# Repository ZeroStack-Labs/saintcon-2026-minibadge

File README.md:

<h1><span style="color:#A3FF12">ZeroStack Labs SAINTCON 2026 MiniBadge</span></h1>

A custom SAINTCON-compatible MiniBadge designed as a ZeroStack Labs hardware/firmware learning project.

This project combines PCB design, embedded firmware, 3D printing, mechanical design, and custom fabrication into a small badge intended for use with the SAINTCON MiniBadge ecosystem.

The finished design features an ATtiny402 microcontroller, two green LEDs, a custom two-color 3D-printed topper, and a dedicated UPDI programming/test jig.

> **Project status:** Prototype / active development  
> The PCB has been ordered and the 3D-printed topper design has reached a successful production prototype.

---

## Features

- SAINTCON MiniBadge-compatible footprint and pinout
- Custom 25.4 mm × 25.4 mm PCB
- ATtiny402 microcontroller
- Two individually controlled green LEDs
- UPDI programming test point
- Custom ZeroStack Labs silkscreen artwork
- Two-color 3D-printed topper
- Acid-green translucent logo/inlay
- Black structural backing layer
- M2 self-tapping mounting screws
- Custom 3D-printed programming jig
- Planned LED breathing / animation firmware

---

## Project Goals

This project started as a way to learn more about:

- KiCad PCB design
- Embedded microcontrollers
- UPDI programming
- Surface-mount soldering
- PCB fabrication
- Multi-color 3D printing
- Mechanical integration between a PCB and printed topper
- Firmware development for small embedded devices

The design files are being published so others can study the project, modify it, and create their own MiniBadge variations.

---

## Hardware

### Microcontroller

The badge uses a **Microchip ATtiny402-SSN** in an SOIC-8 package.

| ATtiny402 Pin | Function               |
| ------------- | ---------------------- |
| VCC           | +3.3 V                 |
| GND           | Ground                 |
| PA1           | LED 1                  |
| PA2           | LED 2                  |
| PA0 / UPDI    | Programming test point |

Unused pins are intentionally left unconnected.

### LEDs

Two green 1206 LEDs are driven through 220 ohm current-limiting resistors.

Approximate LED current:

```text
(3.3 V - 2.1 V) / 220 ohm ≈ 5.5 mA
```

### Decoupling

A 0.1 uF ceramic capacitor is placed close to the ATtiny402 VCC and GND pins.

---

## MiniBadge Interface

The PCB follows the open MiniBadge pinout and interface convention.

Relevant pins used by this design include:

| Pin | Function |
| --- | -------- |
| 1   | VBATT    |
| 2   | GND      |
| 7   | +3V3     |
| 8   | GND      |
| 9   | CLK      |
| 10  | NC       |
| 15  | +3V3     |
| 16  | GND      |

Only the required header positions are intended to be populated, while the PCB retains the complete 16-hole MiniBadge footprint.

> **Important:** VBATT and +3V3 are not connected together.

---

## PCB

The PCB was designed in **KiCad 10**.

### Board dimensions

- 25.4 mm × 25.4 mm
- Rounded square outline
- 2 mm corner radius
- Three 2.2 mm mounting holes

### Fabrication

The first production run was ordered through **OSH Park** using the **After Dark** process.

Fabrication outputs include:

- Front copper
- Back copper
- Front solder mask
- Back solder mask
- Front silkscreen
- Back silkscreen
- Edge cuts
- Plated through-hole drill file
- Non-plated through-hole drill file

---

## 3D-Printed Topper

The topper is designed as a two-color print consisting of:

1. A black structural body
2. A translucent green ZeroStack Labs artwork/inlay

The successful production prototype is:

**V10.1**

### Production files

```text
ZeroStack_Topper_FINAL_v10_1_BLACK_BODY.stl
ZeroStack_Topper_FINAL_v10_1_GREEN_INLAY.stl
```

### Printing workflow

The two STL files are imported into **Flash Studio**, assembled as separate objects, and assigned different filaments.

Recommended orientation:

- **Face down**
- **Mounting posts up**

Printing face-down allows the visible surface to inherit the PEI build plate texture while keeping layer lines on the hidden rear surface.

### Topper construction

- Total top plate thickness: 2.0 mm
- Solid black backing: 0.5 mm
- Green inlay depth: 1.5 mm
- Mounting post diameter: approximately 4.5 mm
- M2 self-tapping pilot hole: approximately 1.7 mm

The mounting posts use a reinforced/tapered base to improve print reliability.

---

## Programming Jig

A custom 3D-printed jig was created to simplify programming and testing.

The jig uses the MiniBadge header locations to position the PCB and provides access to the ATtiny402 UPDI test point.

The intended programming setup uses:

- MiniBadge +3V3
- MiniBadge GND
- One pogo pin contacting the UPDI test pad

An Arduino Uno R3 may be used as a UPDI programmer with suitable firmware/software.

Programming documentation will be added as the firmware workflow is finalized.

---

## Firmware

Firmware is planned for the ATtiny402 to control both LEDs.

Initial goals include:

- Smooth breathing animation
- Adjustable brightness
- Adjustable breathing speed
- Optional alternating LED phase
- Simple constants for easy customization

---

## Repository Structure

```text
saintcon-2026-minibadge/
├── README.md
├── LICENSE
├── hardware/
│   ├── pcb/
│   ├── gerbers/
│   └── bom/
├── mechanical/
│   ├── topper/
│   └── programming-jig/
├── firmware/
├── docs/
└── assets/
```

---

## Bill of Materials

| Qty / Badge        | Component           | Part                    |
| ------------------ | ------------------- | ----------------------- |
| 1                  | Microcontroller     | Microchip ATtiny402-SSN |
| 1                  | 0.1 uF capacitor    | KEMET C0805C104K8RACTU  |
| 2                  | 220 ohm resistor    | Yageo RC1206FR-07220RL  |
| 2                  | Green LED           | Kingbright APTL3216CGCK |
| 4 × 2-pin sections | 2.54 mm male header | Sullins PREC040SAAN-RC  |

Additional parts include mounting screws and the printed topper.

---

## Assembly Notes

Recommended assembly order:

1. Inspect the bare PCB.
2. Solder the ATtiny402.
3. Solder the 0.1 uF decoupling capacitor.
4. Solder the two 220 ohm resistors.
5. Solder the two LEDs.
6. Check for shorts between +3V3 and GND.
7. Program and test the ATtiny402.
8. Install the MiniBadge headers.
9. Attach the printed topper.
10. Perform final functional testing.

For a batch build, fully assemble and test **one badge first** before assembling the remainder.

---

## Credits

This project would not exist without the work of **Luke Jenkins and the contributors to the MiniBadge standard**.

The PCB interface and footprint used in this project are based on the open MiniBadge project:

**https://github.com/lukejenkins/minibadge**

The MiniBadge project provided the pinout, footprint convention, and reference material used as the foundation for this SAINTCON-compatible design.

Huge thanks to the original authors and contributors for making the standard and design resources publicly available.

---

## Disclaimer

This project was created as a learning project by a beginner in PCB and embedded hardware design.

While the design has been reviewed and tested to the best of my ability, it may contain mistakes, design limitations, or implementation issues.

**Use these files at your own risk.**

Before manufacturing, assembling, modifying, or powering the design, independently verify:

- Schematic connections
- PCB layout
- Component orientation
- Component ratings
- Power requirements
- Firmware behavior
- Mechanical clearances

ZeroStack Labs and the project author are not responsible for damage to hardware, components, tools, computers, programmers, host devices, or other equipment resulting from the use or modification of this project.

---

## License

This project is intended to be open source and is released under the **MIT License**, unless otherwise noted for third-party assets or referenced projects.

You are welcome to:

- Study the design
- Modify it
- Build your own version
- Create derivative projects
- Use the files as a learning resource

Please preserve any required third-party attribution where applicable.

---

## About ZeroStack Labs

**ZeroStack Labs** is a personal technology lab focused on learning, experimentation, cybersecurity, software development, hardware projects, 3D printing, and hands-on technical education.

This MiniBadge is one of the first hardware projects developed under the ZeroStack Labs name.

---

## Future Work

Planned additions include:

- ATtiny402 breathing LED firmware
- UPDI programming guide
- Assembly photos
- Soldering notes
- Final PCB photos
- Completed badge photos
- Programming jig documentation
- Alternate topper colors / special editions
- Video build series for the ZeroStack Labs YouTube channel

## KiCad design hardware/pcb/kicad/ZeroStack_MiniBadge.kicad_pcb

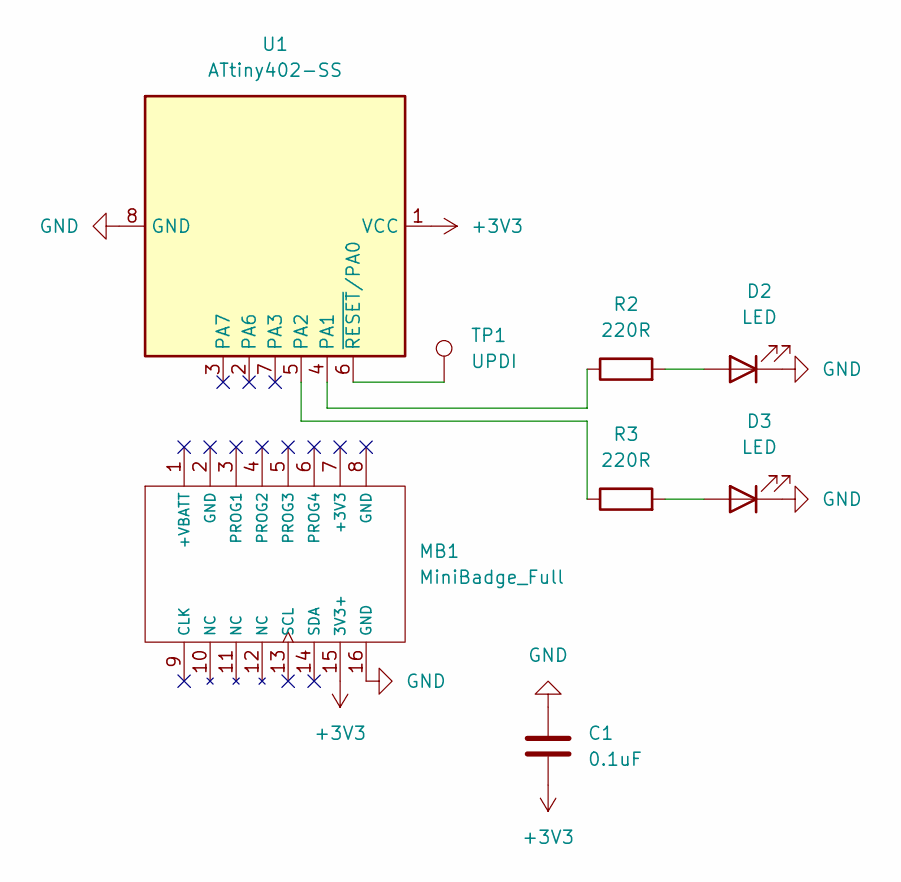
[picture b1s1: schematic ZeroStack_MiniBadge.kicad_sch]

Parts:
C1: 0.1uF; C_0805_2012Metric
D2, D3: LED; LED_1206_3216Metric
MB1: MiniBadge_Full; ZS_MiniBadge_Full_NoEdges
R2, R3: 220R; R_1206_3216Metric
TP1: UPDI; TestPoint_Pad_D1.5mm
U1: ATtiny402-SS; SOIC-8_3.9x4.9mm_P1.27mm

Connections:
+3V3: C1.2, MB1.15 (3V3+), U1.1 (VCC)
GND: C1.1, D2.1 (K), D3.1 (K), MB1.16 (GND), U1.8 (GND)
unnamed: D2.2 (A), R2.2
unnamed: D3.2 (A), R3.2
unnamed: R2.1, U1.4 (PA1)
unnamed: R3.1, U1.5 (PA2)
unnamed: TP1.1 (1_1), U1.6 (~RESET/PA0)

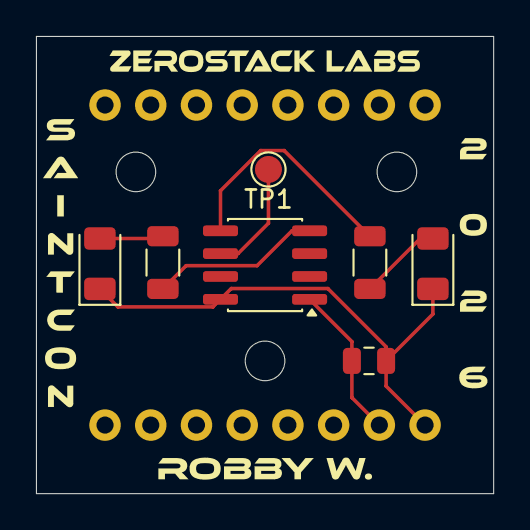
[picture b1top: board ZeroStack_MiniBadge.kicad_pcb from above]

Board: 2 copper layers, 25.4 x 25.4 mm, 8 parts (0 on the bottom side), 7 nets.
